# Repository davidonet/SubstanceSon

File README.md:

# Hardware

* Raspberry Pi [http://www.raspberrypi.org/]
* I2C 16 Channel PWM Servo & SPI 23017 x1 - 16 GPIO Board [http://www.pridopia.co.uk/pi-9685-23017-lp.html]
* Occidentalis v0.2 [https://learn.adafruit.com/adafruit-raspberry-pi-educational-linux-distro/occidentalis-v0-dot-2]
* 16 mosfet board to drive vibrator
* Power supply

# OSC messages

## continuous duty cycle control message
Send to a specific vibrator a pwm percent

    osc:/pwm <vibrator #> <pwm %>

Send 0% to stop

## pulse message
generate a millisecond pulse on specific vibrator

    osc:/pulse <vibrator #> <duration in ms>

## note from midi translator 
Vibrator #0 is C3 note, velocity is converted in pwm percent

    osc:/midi/note/<channel> <pitch> <velocity> <trigger>

## control change from midi translator
vibrator power can adjust with control change. In order to keep standard midi label vibrator #0 is cc 16

    osc:/midi/cc<number>/<channel> <value>
    
Midi translation is based on osculator specifications : [http://dl.osculator.net/doc/OSCulator+2.11+Manual.pdf]

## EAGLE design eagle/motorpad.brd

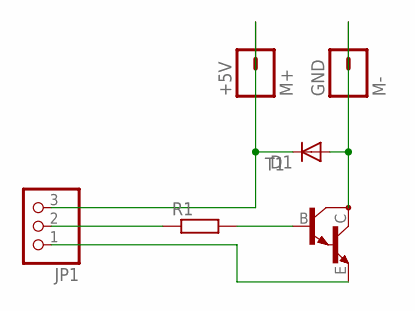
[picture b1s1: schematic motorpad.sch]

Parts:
+5V: M+; 1X01_OFFSET
D1: DIODESOD; SOD-323
GND: M-; 1X01_OFFSET
JP1: PINHD-1X3/90; 1X03/90
R1: R-EU_R0603; R0603
T1: MMBTA13LT1-NPN_DARL-SOT23-BEC; SOT23-BEC

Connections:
GND: JP1.1, T1.E
unnamed: JP1.2, R1.1
unnamed: R1.2, T1.B
unnamed: D1.2 (A), GND.1, T1.C
unnamed: +5V.1, D1.1 (C), JP1.3

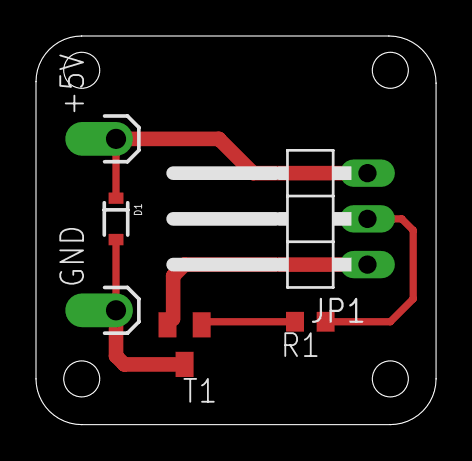
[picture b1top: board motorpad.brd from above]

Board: 2 copper layers, 22.2 x 21.6 mm, 6 parts (0 on the bottom side), 5 nets.

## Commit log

2013-12-14 adding x bit
2013-12-14 note handling
2013-12-14 channel 0 is midi C4
2013-12-14 Shifting to C1
2013-12-14 longer test
2013-12-14 speed bug
2013-12-14 speeding test
2013-12-14 Implementing Control Change
2014-06-27 Adding osc protocol
2014-06-27 Adding hardware description
2014-11-06 Adding eagle files

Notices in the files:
parts and their libraries:
SparkFun-DiscreteSemi: Licensing: CC v3.0 Share-Alike You are welcome to use this library for commercial purposes.
